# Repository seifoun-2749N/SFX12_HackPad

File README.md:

# SFX12 HackPad

<div align="center">

**A custom 12-key macropad with rotary encoder and SK6812 RGB LEDs.**

</div>

---

## Overview :

A custom macropad made with 12 mechanical switches and a rotay encoder with creative and chic design . It's also an open source device that you can build it yourself and costumize it like you want. 

---

## Features :

- 12 mechanical switches
- Rotary encoder
- 5 * SK6812 RGB LEDs 
- Tap dance on every key
- 12 app launchers
- Dedicated shortcut row

---

## Hardware :

* Seeeduino XIAO (1) SAMD21G18
* mechanical switches (12) MX-compatible
* EC11 (1) Rotary encoder with push button
* SK6812 (5) addressable RGB LEDs
* 1N4148 (12) signal diodes

---

## PCB and Shematics :

### PCB Front

### PCB Back

### Schematic

---

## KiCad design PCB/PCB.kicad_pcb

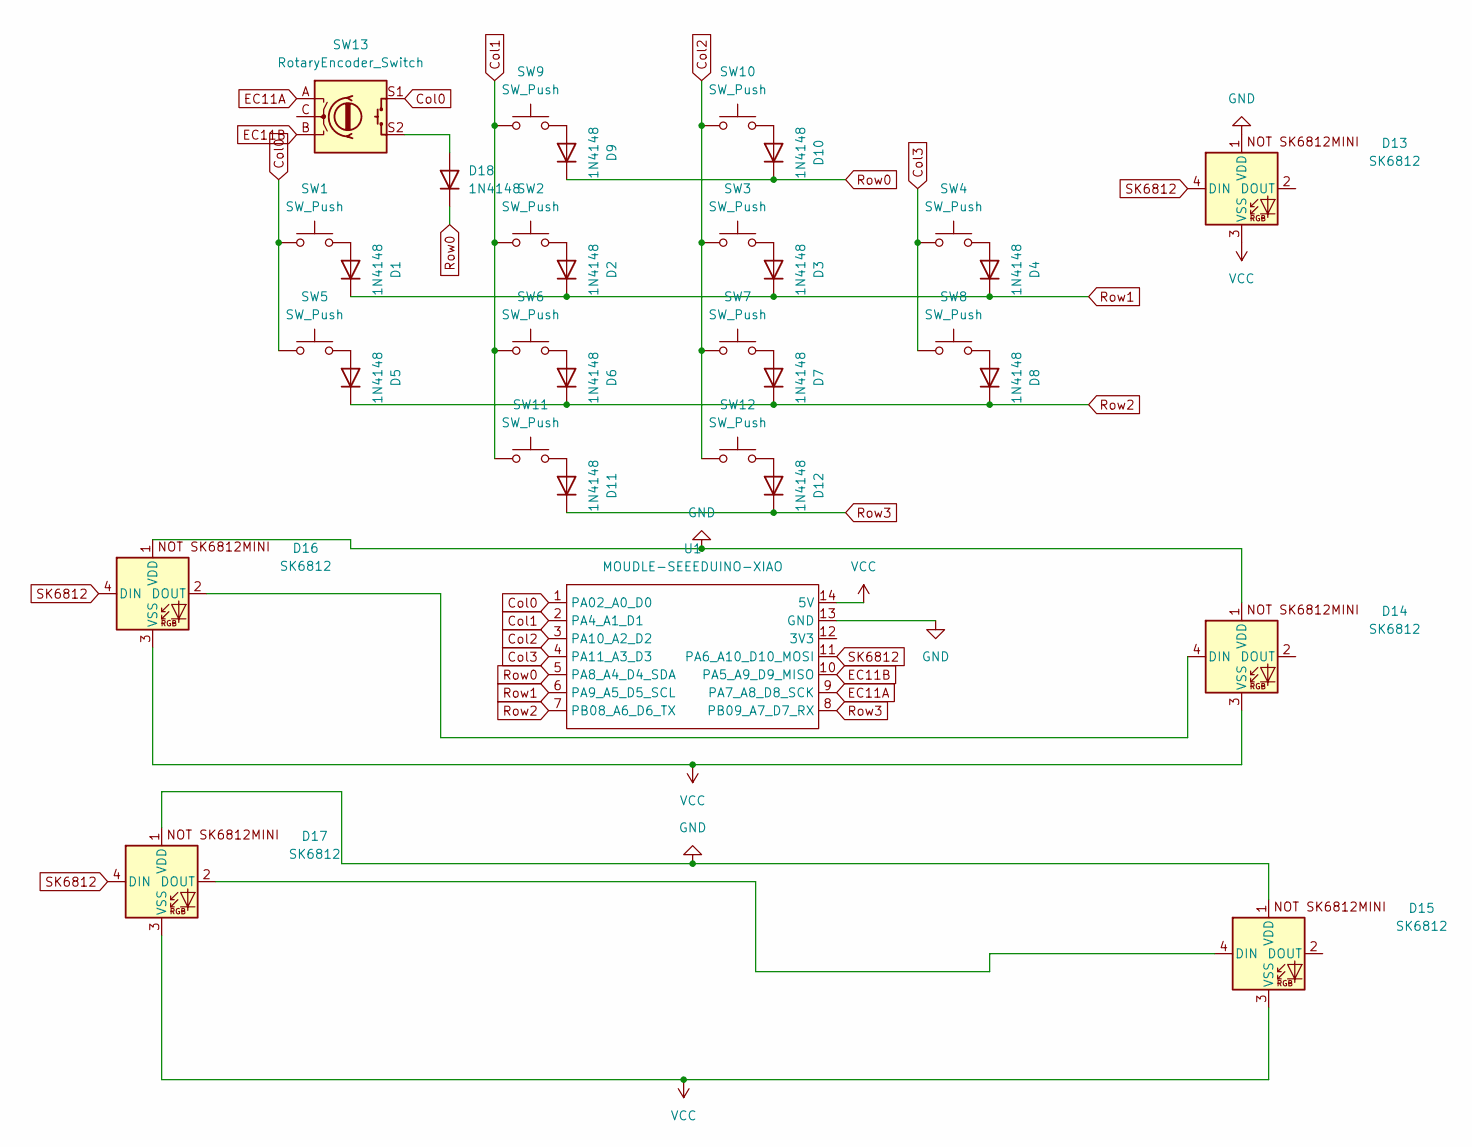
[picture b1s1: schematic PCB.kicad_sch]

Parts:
D1, D2, D3, D4, D5, D6, D7, D8, D9, D10, D11, D12, D18: 1N4148; D_DO-35_SOD27_P7.62mm_Horizontal
D13, D14, D15, D16, D17: SK6812; SK6812MINI-E - 3.2x2.8x1.78mm
SW1, SW2, SW3, SW4, SW5, SW6, SW7, SW8, SW9, SW10, SW11, SW12: SW_Push; SW_Cherry_MX_1.00u_PCB
SW13: RotaryEncoder_Switch; RotaryEncoder_Alps_EC11E-Switch_Vertical_H20mm
U1: MOUDLE-SEEEDUINO-XIAO; XIAO-Generic-Hybrid-14P-2.54-21X17.8MM

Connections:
Col0: SW1.1, SW5.1, SW13.S1, U1.1 (PA02_A0_D0)
Col1: SW2.1, SW6.1, SW9.1, SW11.1, U1.2 (PA4_A1_D1)
Col2: SW3.1, SW7.1, SW10.1, SW12.1, U1.3 (PA10_A2_D2)
Col3: SW4.1, SW8.1, U1.4 (PA11_A3_D3)
EC11A: SW13.A, U1.9 (PA7_A8_D8_SCK)
EC11B: SW13.B, U1.10 (PA5_A9_D9_MISO)
GND: D13.1 (VDD), D14.1 (VDD), D15.1 (VDD), D16.1 (VDD), D17.1 (VDD), U1.13 (GND)
unnamed: D1.2 (A), SW1.2
unnamed: D2.2 (A), SW2.2
unnamed: D3.2 (A), SW3.2
unnamed: D4.2 (A), SW4.2
unnamed: D5.2 (A), SW5.2
unnamed: D6.2 (A), SW6.2
unnamed: D7.2 (A), SW7.2
unnamed: D8.2 (A), SW8.2
unnamed: D9.2 (A), SW9.2
unnamed: D10.2 (A), SW10.2
unnamed: D11.2 (A), SW11.2
unnamed: D12.2 (A), SW12.2
unnamed: D14.4 (DIN), D16.2 (DOUT)
unnamed: D15.4 (DIN), D17.2 (DOUT)
unnamed: D18.2 (A), SW13.S2
Row0: D9.1 (K), D10.1 (K), D18.1 (K), U1.5 (PA8_A4_D4_SDA)
Row1: D1.1 (K), D2.1 (K), D3.1 (K), D4.1 (K), U1.6 (PA9_A5_D5_SCL)
Row2: D5.1 (K), D6.1 (K), D7.1 (K), D8.1 (K), U1.7 (PB08_A6_D6_TX)
Row3: D11.1 (K), D12.1 (K), U1.8 (PB09_A7_D7_RX)
SK6812: D13.4 (DIN), D16.4 (DIN), D17.4 (DIN), U1.11 (PA6_A10_D10_MOSI)
VCC: D13.3 (VSS), D14.3 (VSS), D15.3 (VSS), D16.3 (VSS), D17.3 (VSS), U1.14 (5V)

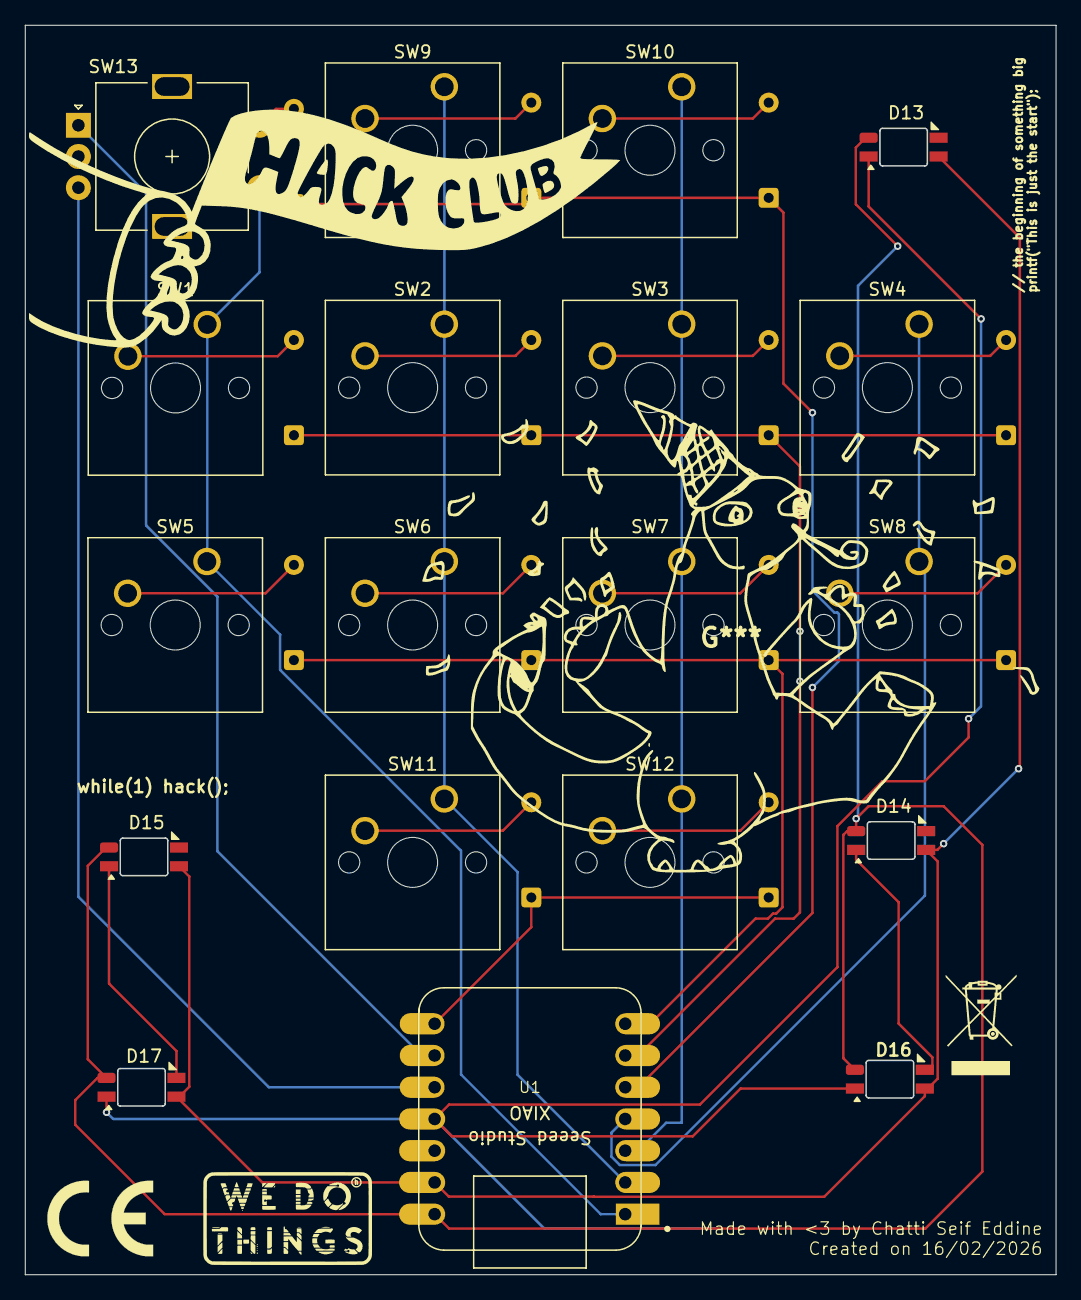
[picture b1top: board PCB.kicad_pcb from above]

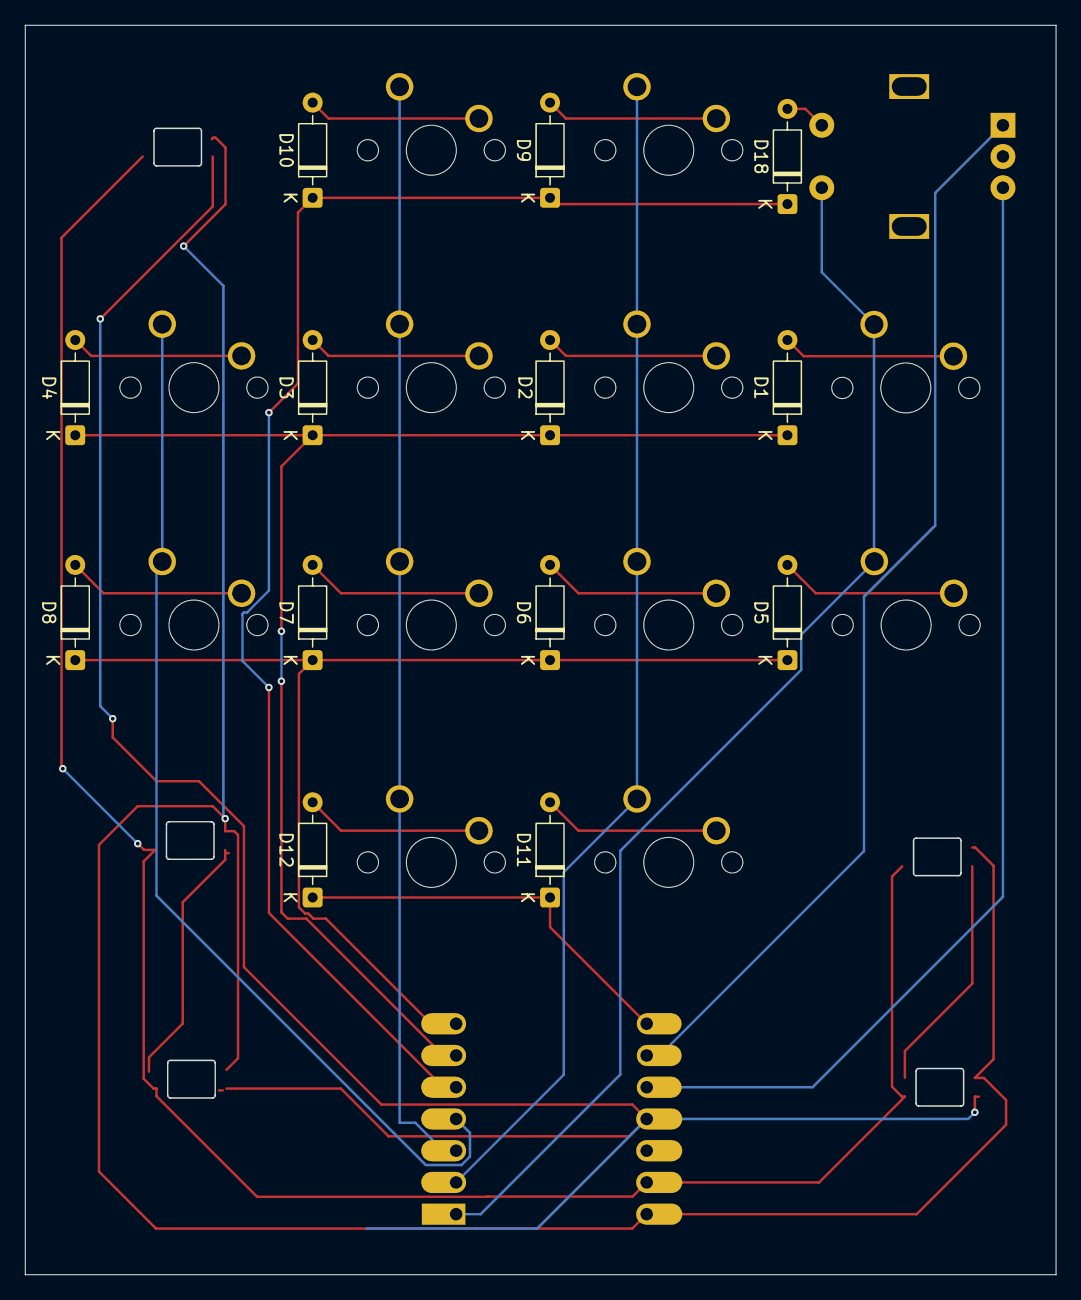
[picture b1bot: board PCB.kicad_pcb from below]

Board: 2 copper layers, 82.4 x 99.9 mm, 32 parts (13 on the bottom side), 28 nets.
